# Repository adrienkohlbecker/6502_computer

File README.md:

# 6502 computer

## Board

## Schematic

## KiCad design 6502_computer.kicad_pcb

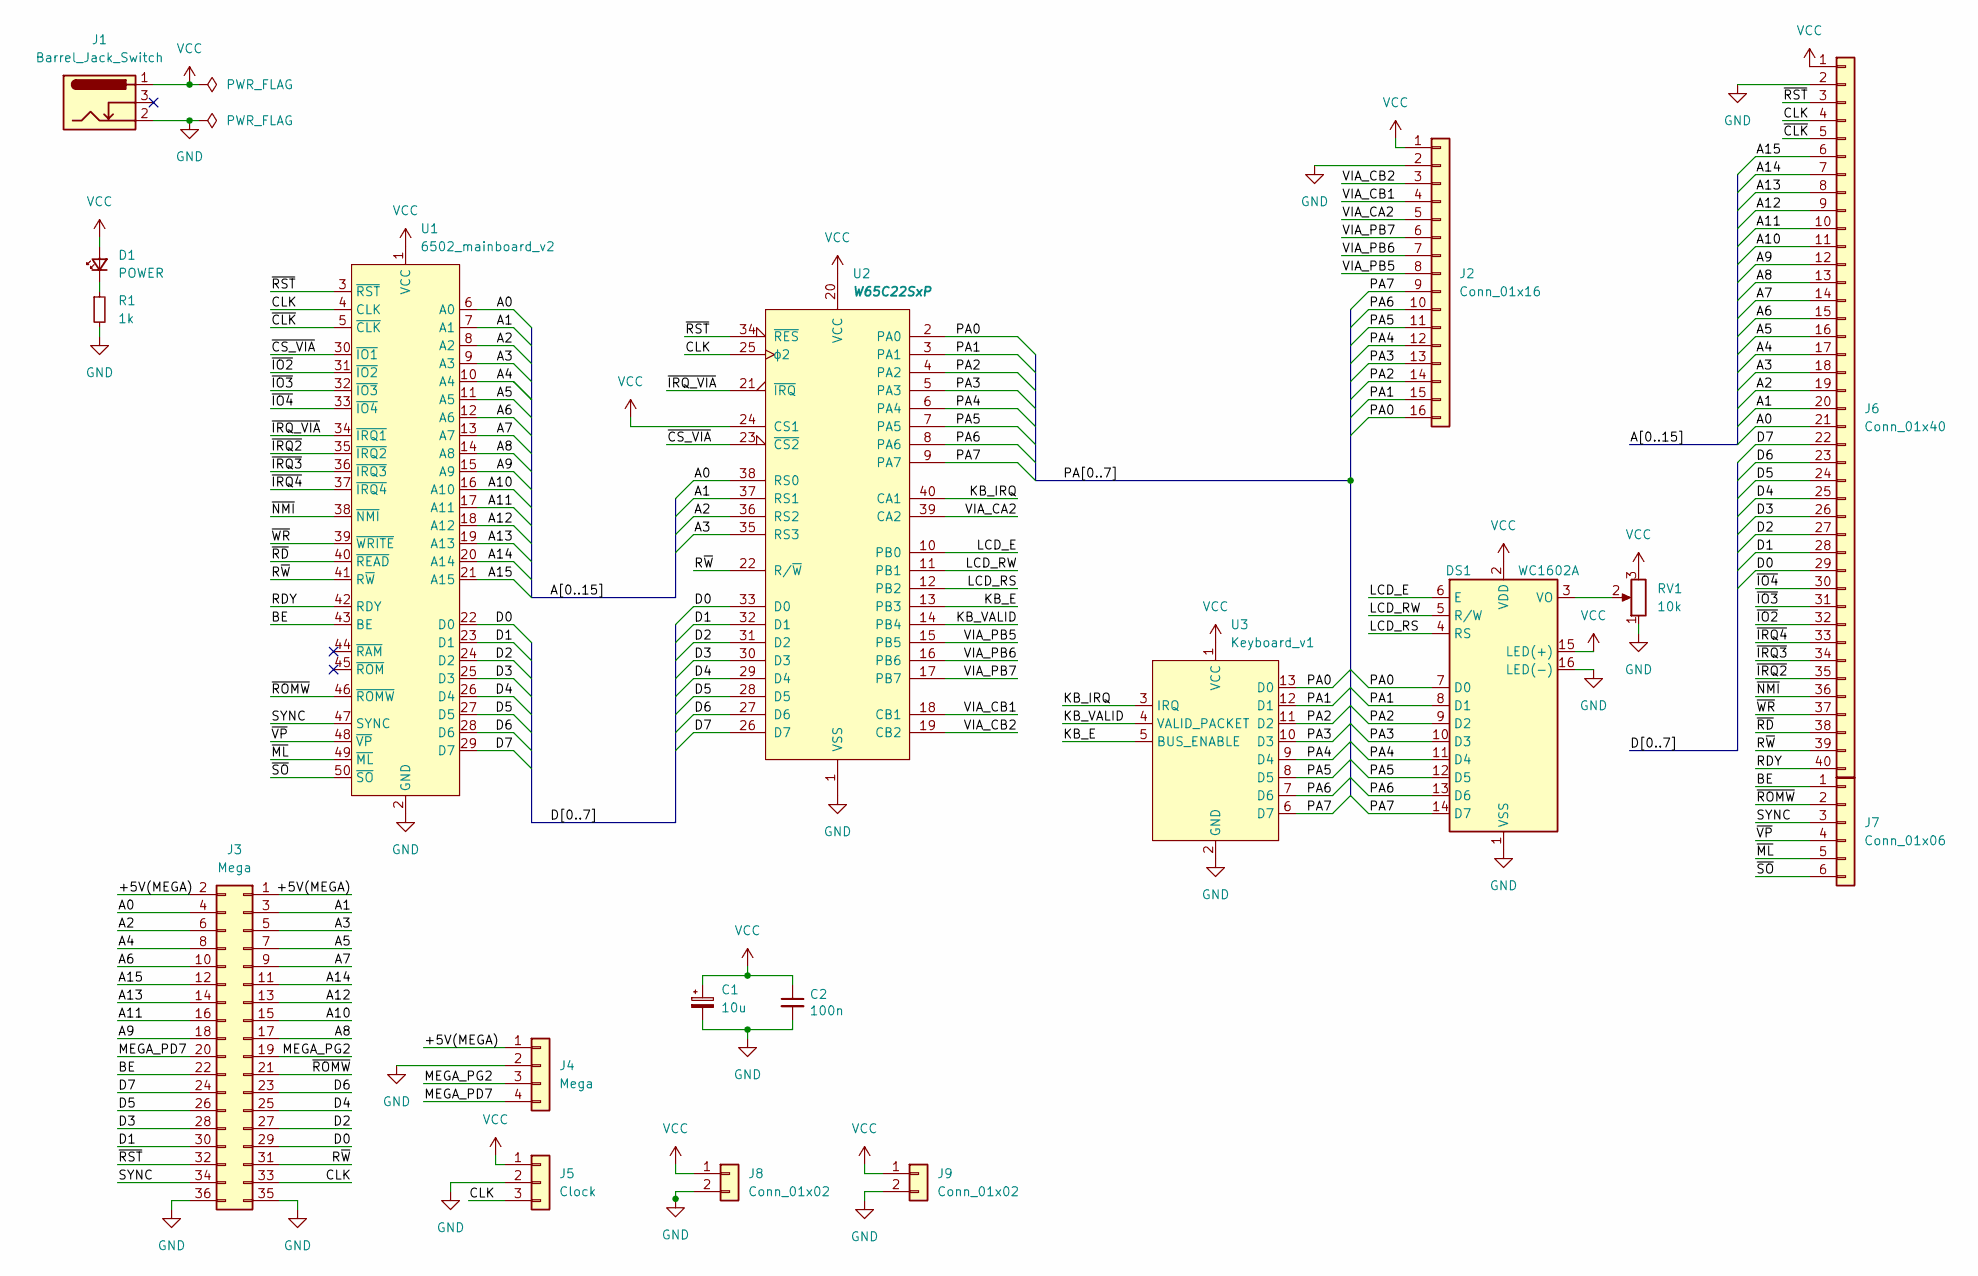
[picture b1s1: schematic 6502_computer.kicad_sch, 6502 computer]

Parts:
C1: 10u; CP_Radial_D4.0mm_P1.50mm
C2: 100n; C_Disc_D5.0mm_W2.5mm_P5.00mm
D1: POWER; LED_D3.0mm
DS1: WC1602A
J1: Barrel_Jack_Switch; BarrelJack_Horizontal
J2: Conn_01x16; PinSocket_1x16_P2.54mm_Vertical
J3: Mega; PinHeader_2x18_P2.54mm_Vertical
J4: Mega; PinSocket_1x04_P2.54mm_Vertical
J5: Clock; PinSocket_1x03_P2.54mm_Vertical
J6: Conn_01x40; PinSocket_1x40_P2.54mm_Vertical
J7: Conn_01x06; PinSocket_1x06_P2.54mm_Vertical
J8, J9: Conn_01x02; PinSocket_1x02_P2.54mm_Vertical
R1: 1k; R_Axial_DIN0207_L6.3mm_D2.5mm_P7.62mm_Horizontal
RV1: 10k; Potentiometer_Vishay_T7-YA_Single_Vertical
U1: 6502_mainboard_v2; Mainboard v2
U2: W65C22SxP; DIP-40_W15.24mm
U3: Keyboard_v1; Keyboard v1

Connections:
/+5V(MEGA): J3.1, J3.2, J4.1
/A0: J3.4, J6.21, U1.6 (A0), U2.38 (RS0)
/A1: J3.3, J6.20, U1.7 (A1), U2.37 (RS1)
/A2: J3.6, J6.19, U1.8 (A2), U2.36 (RS2)
/A3: J3.5, J6.18, U1.9 (A3), U2.35 (RS3)
/A4: J3.8, J6.17, U1.10 (A4)
/A5: J3.7, J6.16, U1.11 (A5)
/A6: J3.10, J6.15, U1.12 (A6)
/A7: J3.9, J6.14, U1.13 (A7)
/A8: J3.17, J6.13, U1.14 (A8)
/A9: J3.18, J6.12, U1.15 (A9)
/A10: J3.15, J6.11, U1.16 (A10)
/A11: J3.16, J6.10, U1.17 (A11)
/A12: J3.13, J6.9, U1.18 (A12)
/A13: J3.14, J6.8, U1.19 (A13)
/A14: J3.11, J6.7, U1.20 (A14)
/A15: J3.12, J6.6, U1.21 (A15)
/BE: J3.22, J7.1, U1.43 (BE)
/CLK: J3.33, J5.3, J6.4, U1.4 (CLK), U2.25 (ϕ2)
/D0: J3.29, J6.29, U1.22 (D0), U2.33 (D0)
/D1: J3.30, J6.28, U1.23 (D1), U2.32 (D1)
/D2: J3.27, J6.27, U1.24 (D2), U2.31 (D2)
/D3: J3.28, J6.26, U1.25 (D3), U2.30 (D3)
/D4: J3.25, J6.25, U1.26 (D4), U2.29 (D4)
/D5: J3.26, J6.24, U1.27 (D5), U2.28 (D5)
/D6: J3.23, J6.23, U1.28 (D6), U2.27 (D6)
/D7: J3.24, J6.22, U1.29 (D7), U2.26 (D7)
/KB_E: U2.13 (PB3), U3.5 (BUS_ENABLE)
/KB_IRQ: U2.40 (CA1), U3.3 (IRQ)
/KB_VALID: U2.14 (PB4), U3.4 (VALID_PACKET)
/LCD_E: DS1.6 (E), U2.10 (PB0)
/LCD_RS: DS1.4 (RS), U2.12 (PB2)
/LCD_RW: DS1.5 (R/W), U2.11 (PB1)
/MEGA_PD7: J3.20, J4.4
/MEGA_PG2: J3.19, J4.3
/PA0: DS1.7 (D0), J2.16, U2.2 (PA0), U3.13 (D0)
/PA1: DS1.8 (D1), J2.15, U2.3 (PA1), U3.12 (D1)
/PA2: DS1.9 (D2), J2.14, U2.4 (PA2), U3.11 (D2)
/PA3: DS1.10 (D3), J2.13, U2.5 (PA3), U3.10 (D3)
/PA4: DS1.11 (D4), J2.12, U2.6 (PA4), U3.9 (D4)
/PA5: DS1.12 (D5), J2.11, U2.7 (PA5), U3.8 (D5)
/PA6: DS1.13 (D6), J2.10, U2.8 (PA6), U3.7 (D6)
/PA7: DS1.14 (D7), J2.9, U2.9 (PA7), U3.6 (D7)
/RDY: J6.40, U1.42 (RDY)
/R~W: J3.31, J6.39, U1.41 (R~W), U2.22 (R/~W)
/SYNC: J3.34, J7.3, U1.47 (SYNC)
/VIA_CA2: J2.5, U2.39 (CA2)
/VIA_CB1: J2.4, U2.18 (CB1)
/VIA_CB2: J2.3, U2.19 (CB2)
/VIA_PB5: J2.8, U2.15 (PB5)
/VIA_PB6: J2.7, U2.16 (PB6)
/VIA_PB7: J2.6, U2.17 (PB7)
/~CLK: J6.5, U1.5 (~CLK)
/~CS_VIA: U1.30 (~IO1), U2.23 (~CS2)
/~IO2: J6.32, U1.31 (~IO2)
/~IO3: J6.31, U1.32 (~IO3)
/~IO4: J6.30, U1.33 (~IO4)
/~IRQ2: J6.35, U1.35 (~IRQ2)
/~IRQ3: J6.34, U1.36 (~IRQ3)
/~IRQ4: J6.33, U1.37 (~IRQ4)
/~IRQ_VIA: U1.34 (~IRQ1), U2.21 (~IRQ)
/~ML: J7.5, U1.49 (~ML)
/~NMI: J6.36, U1.38 (~NMI)
/~RD: J6.38, U1.40 (~READ)
/~ROMW: J3.21, J7.2, U1.46 (~ROMW)
/~RST: J3.32, J6.3, U1.3 (~RST), U2.34 (~RES)
/~SO: J7.6, U1.50 (~SO)
/~VP: J7.4, U1.48 (~VP)
/~WR: J6.37, U1.39 (~WRITE)
GND: C1.2, C2.2, DS1.1 (VSS), DS1.16 (LED(-)), J1.2, J2.2, J3.35, J3.36, J4.2, J5.2, J6.2, J8.2, J9.2, R1.2, RV1.1, U1.2 (GND), U2.1 (VSS), U3.2 (GND)
unnamed: D1.1 (K), R1.1
unnamed: DS1.3 (VO), RV1.2
VCC: C1.1, C2.1, D1.2 (A), DS1.2 (VDD), DS1.15 (LED(+)), J1.1, J2.1, J5.1, J6.1, J8.1, J9.1, RV1.3, U1.1 (VCC), U2.20 (VCC), U2.24 (CS1), U3.1 (VCC)

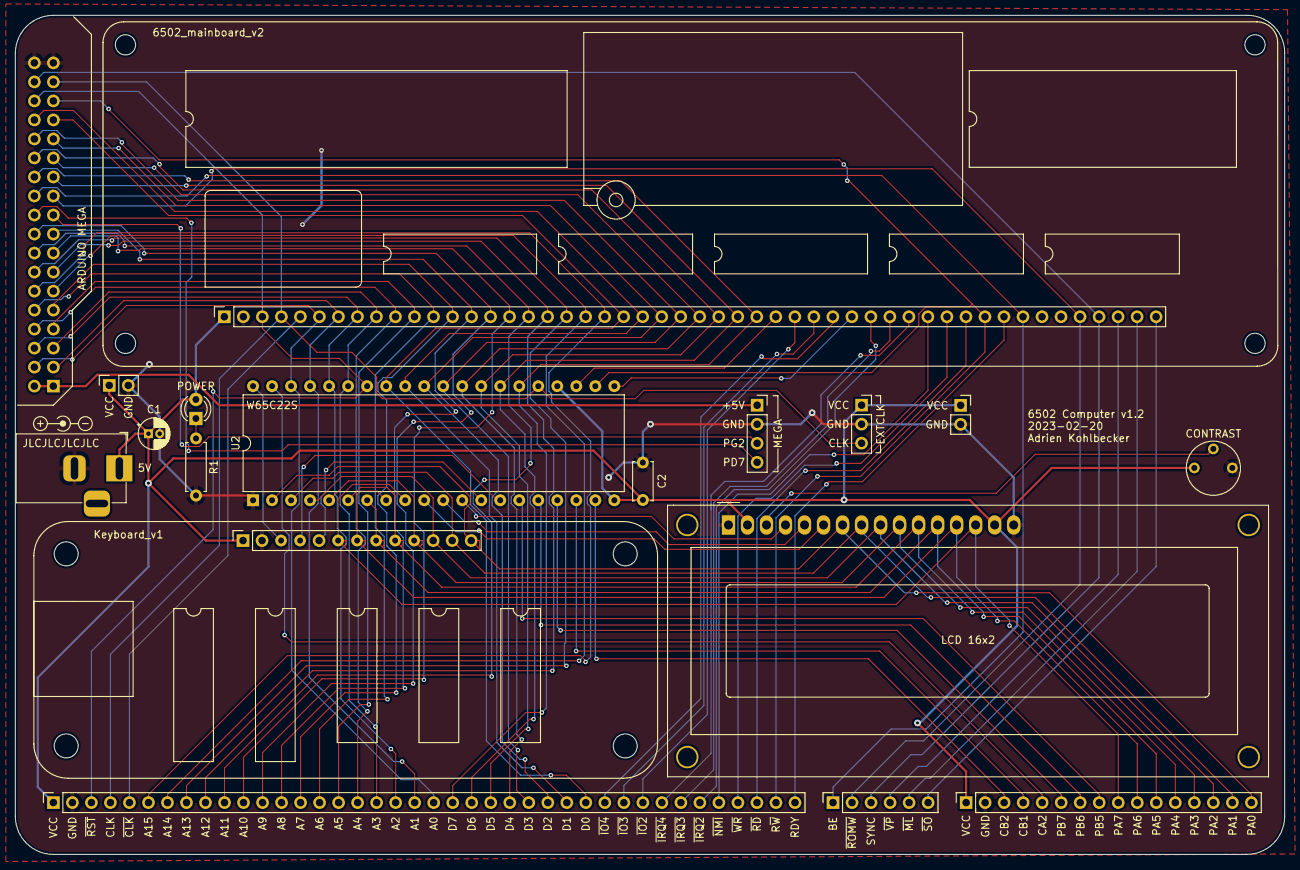
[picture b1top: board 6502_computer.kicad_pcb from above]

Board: 2 copper layers, 169.5 x 112.1 mm, 18 parts (0 on the bottom side), 73 nets.

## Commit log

2022-08-08 Init project
2022-08-30 First board
2023-06-10 Move to two layers

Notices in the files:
6502_computer.kicad_pcb:
Licensed under CERN-OHL-W v2
Copyright © 2022 Adrien Kohlbecker
